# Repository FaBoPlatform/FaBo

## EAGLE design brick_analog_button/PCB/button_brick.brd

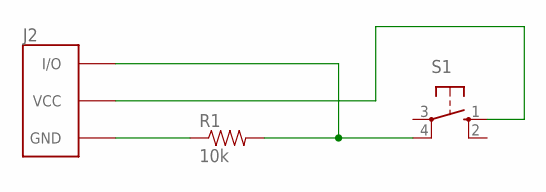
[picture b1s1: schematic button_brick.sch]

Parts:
J2: BRICK_3PIN
R1: 10k; AXIAL-0.4
S1: Button; B3F-10XX

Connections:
GND: J2.GND, R1.P$1 (1)
unnamed: J2.VCC, S1.1 (S)
unnamed: J2.IN/OUT (I/O), R1.P$2 (2), S1.4 (P1)

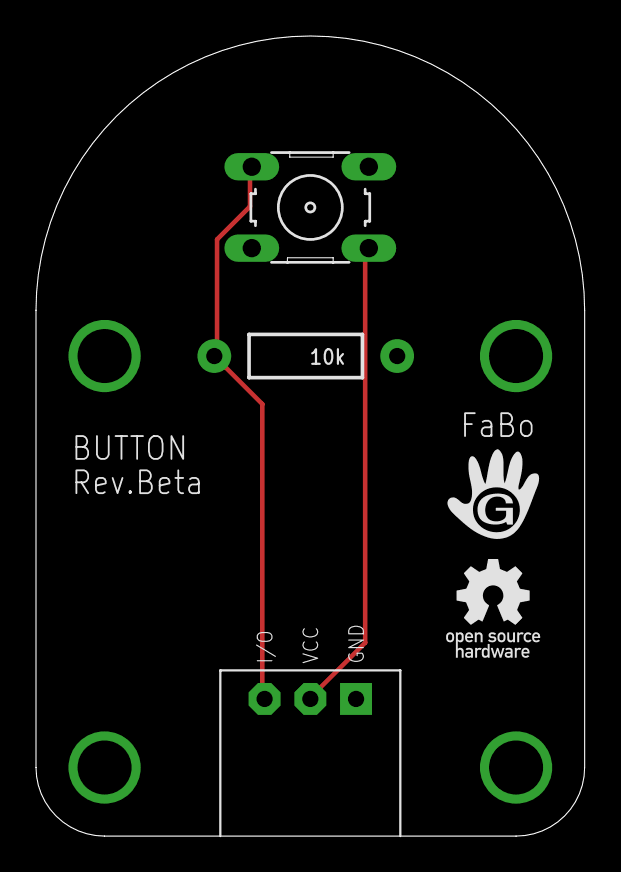
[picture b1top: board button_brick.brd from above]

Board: 2 copper layers, 30.5 x 44.5 mm, 5 parts (0 on the bottom side), 3 nets.

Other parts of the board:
U$2: LOGO_OSHW_T_M
U$3: LOGO_GCLUE_M

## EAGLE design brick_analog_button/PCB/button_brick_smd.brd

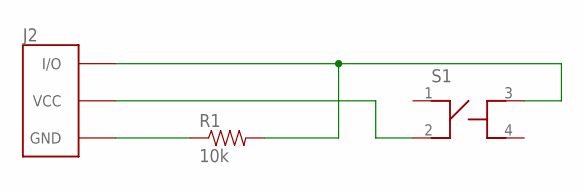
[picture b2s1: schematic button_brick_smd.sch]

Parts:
J2: BRICK_3PIN
R1: 10k; 0603-RES
S1: SWITCH-LS6J2M-T

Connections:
GND: J2.GND, R1.1
unnamed: J2.VCC, S1.2
unnamed: J2.IN/OUT (I/O), R1.2, S1.3

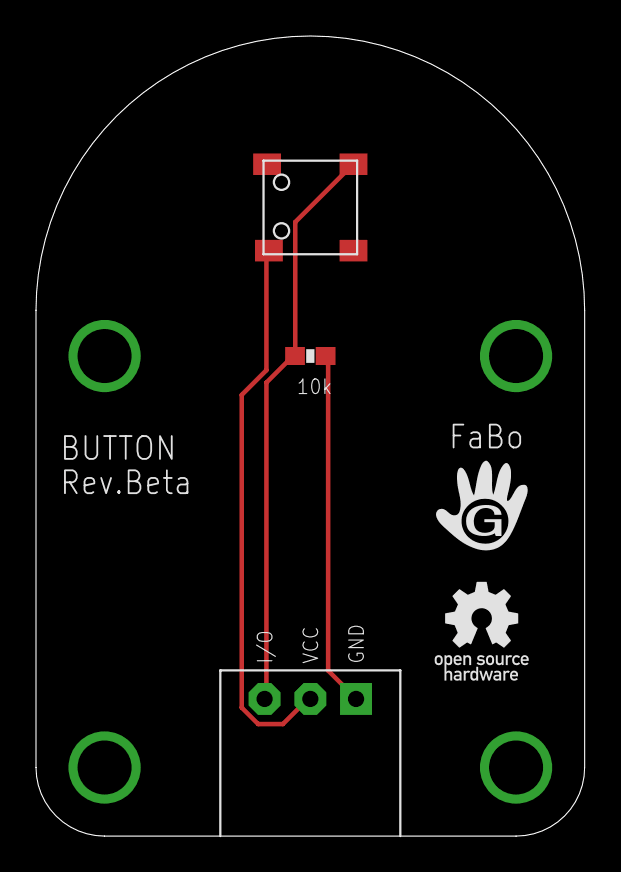
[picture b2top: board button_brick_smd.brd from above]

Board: 2 copper layers, 30.5 x 44.5 mm, 5 parts (0 on the bottom side), 3 nets.

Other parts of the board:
U$1: LOGO_GCLUE_M
U$2: LOGO_OSHW_T_M

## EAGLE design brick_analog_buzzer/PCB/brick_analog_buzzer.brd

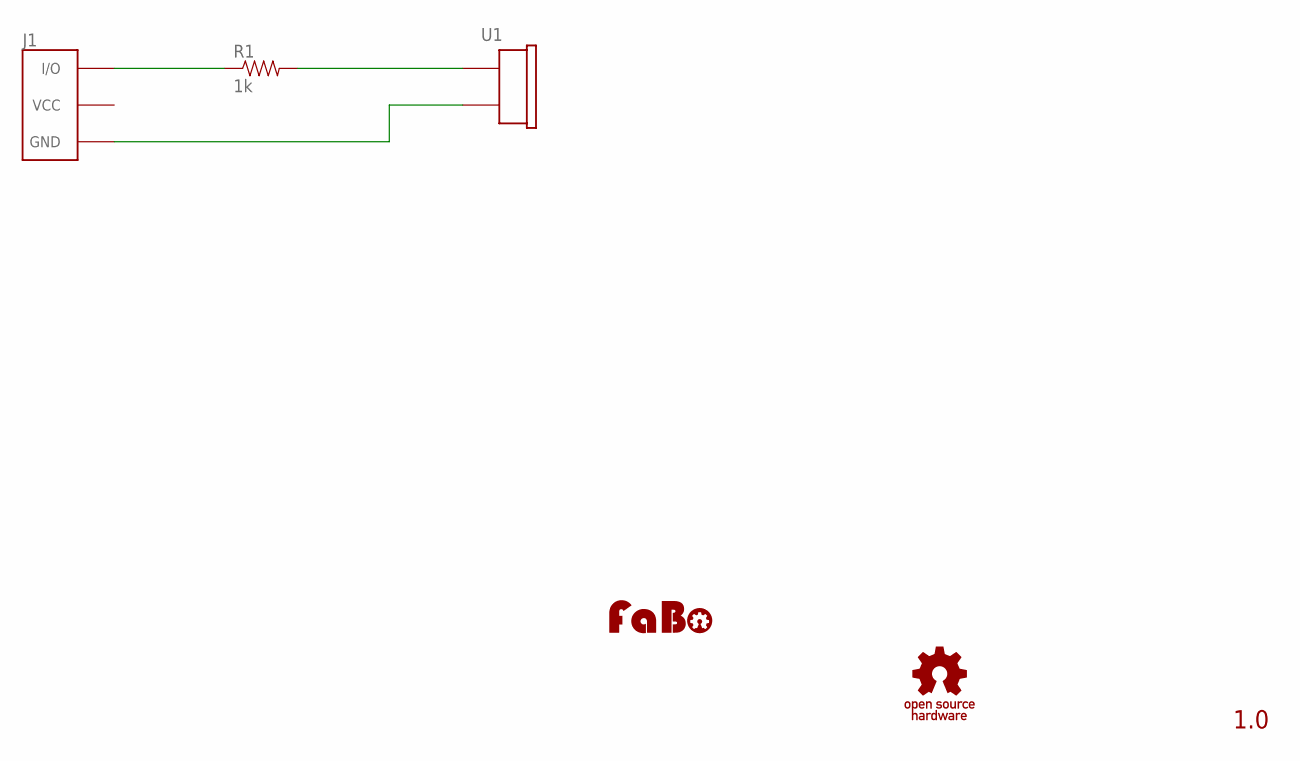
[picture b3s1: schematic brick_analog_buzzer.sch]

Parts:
J1: BRICK_3PIN_NORMAL; BRICK_3PIN
R1: 1k; RES-AXL-REGULAR
U1: BUZZER-PKM13EPYH4000; BUZZER-PKM13EPYH4000-A0
U$2: LOGO_OSHW_T-M; LOGO_OSHW_T_M
U$3: LOGO_FABO-M; LOGO_FABO_M

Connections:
GND: J1.GND, U1.2
unnamed: J1.IN/OUT (I/O), R1.P$1 (1)
unnamed: R1.P$2 (2), U1.1

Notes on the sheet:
1.0

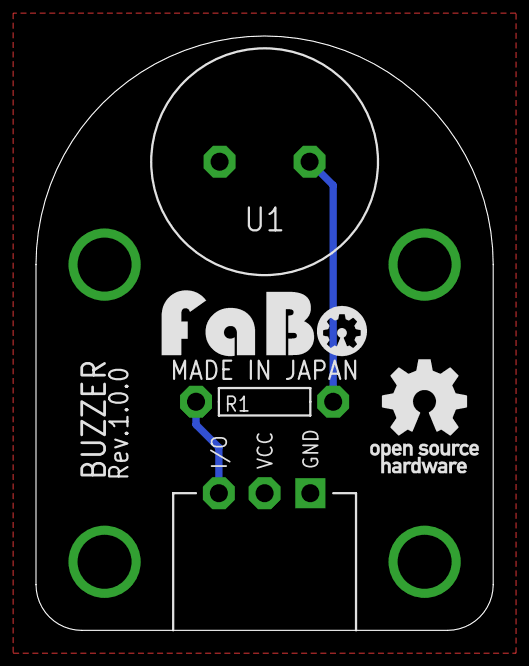
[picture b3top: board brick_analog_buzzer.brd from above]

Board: 2 copper layers, 25.4 x 33.0 mm, 5 parts (0 on the bottom side), 3 nets.

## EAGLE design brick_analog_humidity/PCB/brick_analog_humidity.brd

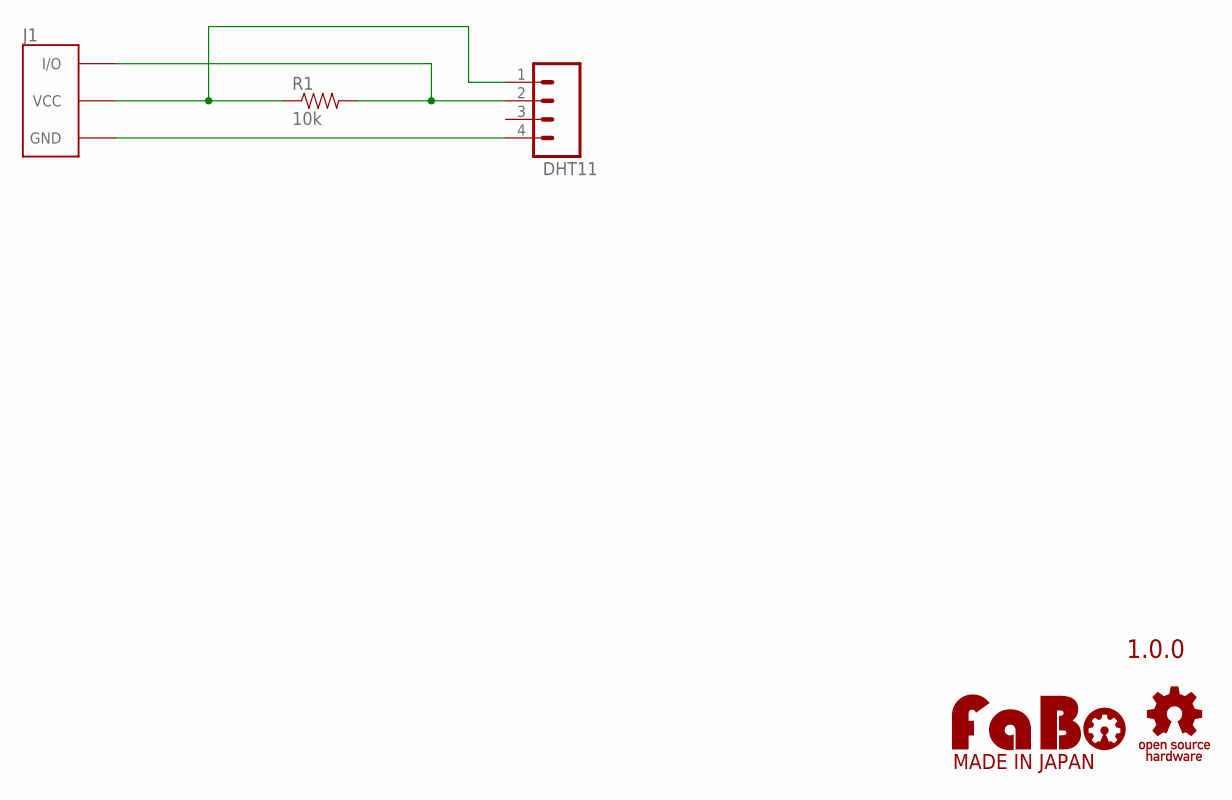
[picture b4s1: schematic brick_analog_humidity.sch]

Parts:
J1: BRICK_3PIN_NORMAL; BRICK_3PIN
JP1: DHT11; 1X04_LONGPADS
R1: 10k; RES-AXL-REGULAR
U$2: LOGO_OSHW-T_M; LOGO_OSHW_T_M
U$3: LOGO_FABO-M; LOGO_FABO_M

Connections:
GND: J1.GND, JP1.4
unnamed: J1.IN/OUT (I/O), JP1.2, R1.P$2 (2)
unnamed: J1.VCC, JP1.1, R1.P$1 (1)

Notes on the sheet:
1.0.0

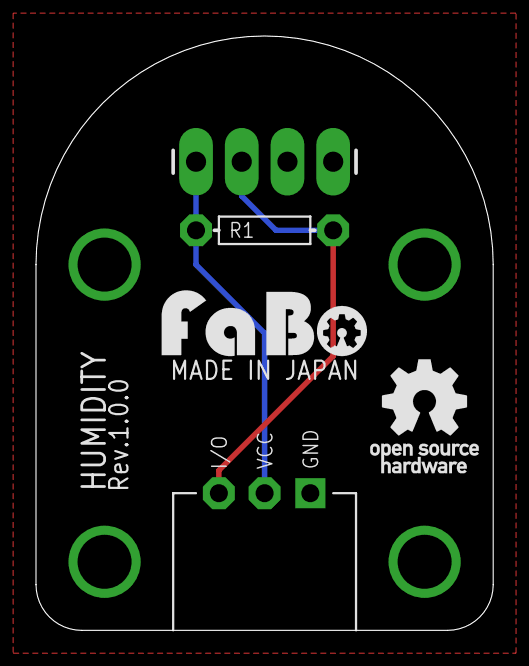
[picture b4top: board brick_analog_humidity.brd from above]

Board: 2 copper layers, 25.4 x 33.0 mm, 5 parts (0 on the bottom side), 3 nets.

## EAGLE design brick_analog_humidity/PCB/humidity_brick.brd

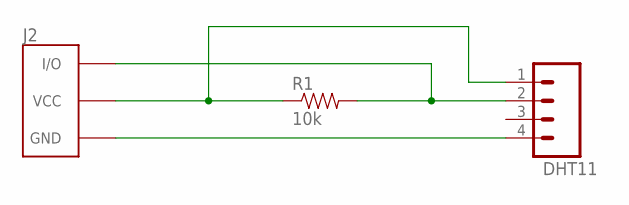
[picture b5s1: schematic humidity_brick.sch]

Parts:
J2: BRICK_3PIN
JP1: DHT11; 1X04_LONGPADS
R1: 10k; AXIAL-0.4

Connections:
GND: J2.GND, JP1.4
unnamed: J2.IN/OUT (I/O), JP1.2, R1.P$2 (2)
unnamed: J2.VCC, JP1.1, R1.P$1 (1)

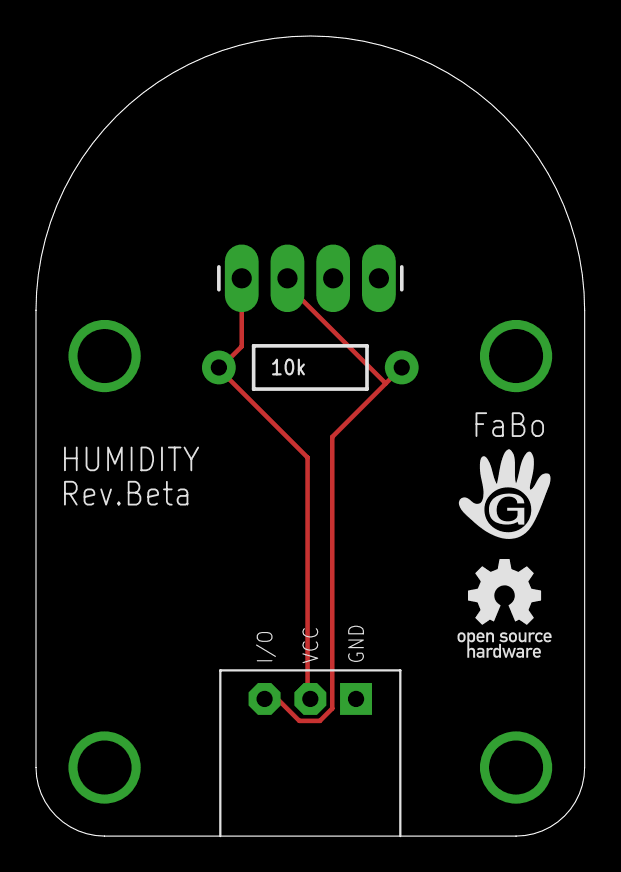
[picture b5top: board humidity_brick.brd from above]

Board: 2 copper layers, 30.5 x 44.5 mm, 5 parts (0 on the bottom side), 3 nets.

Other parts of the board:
U$1: LOGO_OSHW_T_M
U$3: LOGO_GCLUE_M

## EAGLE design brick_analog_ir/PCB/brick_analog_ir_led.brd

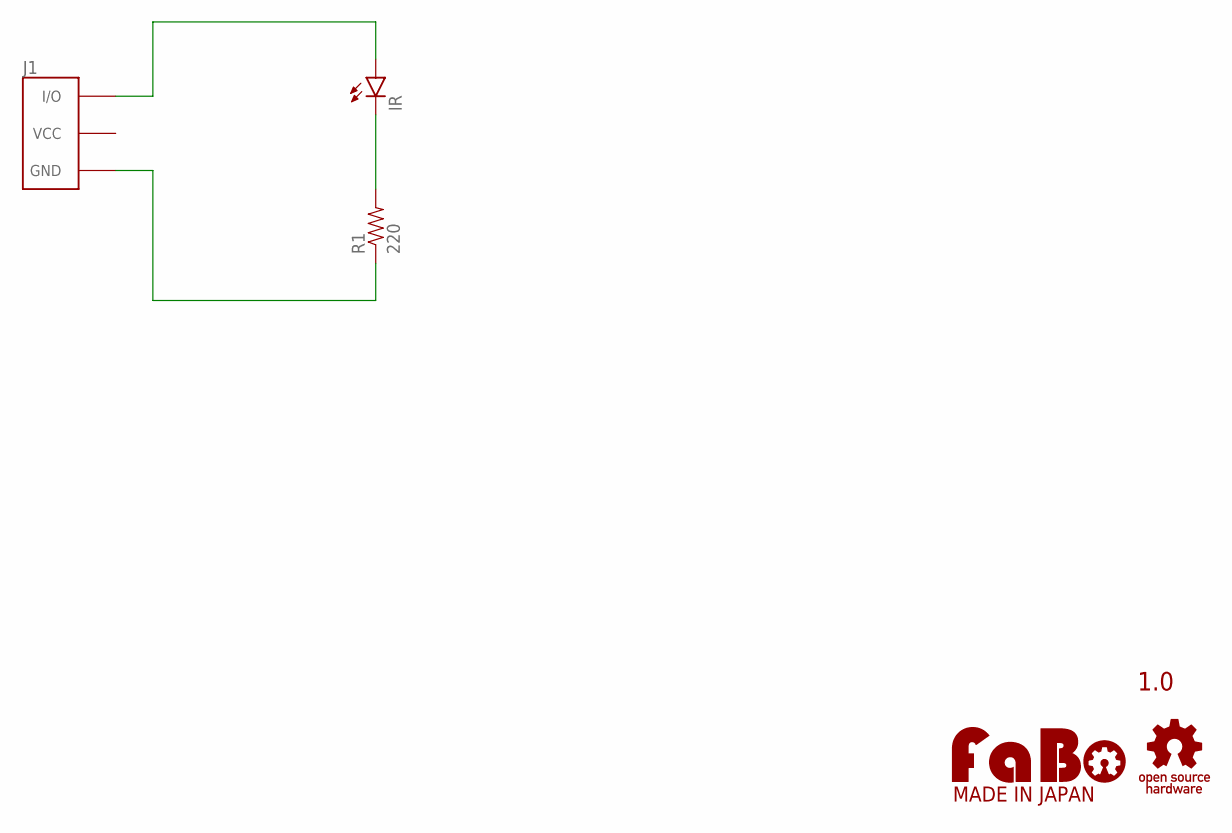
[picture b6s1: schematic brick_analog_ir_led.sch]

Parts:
IR: LED-5MM
J1: FABO_BRICK_3PIN
R1: 220; RES-AXL-REGULAR
U$2: LOGO_FABO-M; LOGO_FABO_M
U$3: LOGO_OSHW-T_M; LOGO_OSHW_T_M

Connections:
GND: J1.GND, R1.P$1 (1)
unnamed: IR.A, J1.IN/OUT (I/O)
unnamed: IR.K (C), R1.P$2 (2)

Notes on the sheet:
1.0

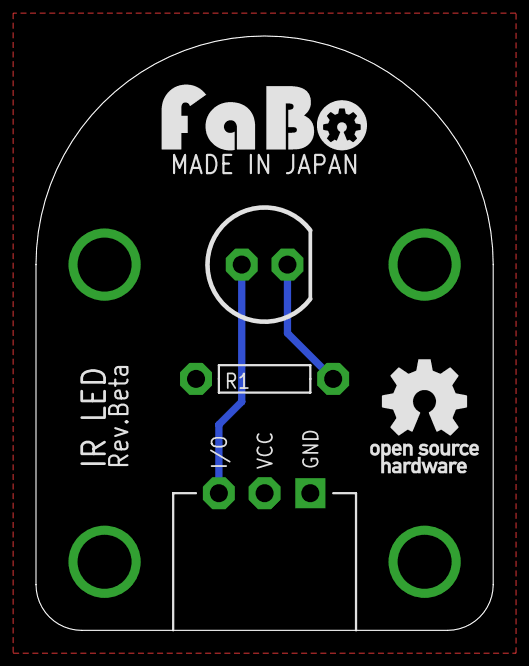
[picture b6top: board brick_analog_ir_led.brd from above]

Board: 2 copper layers, 25.4 x 33.0 mm, 5 parts (0 on the bottom side), 3 nets.

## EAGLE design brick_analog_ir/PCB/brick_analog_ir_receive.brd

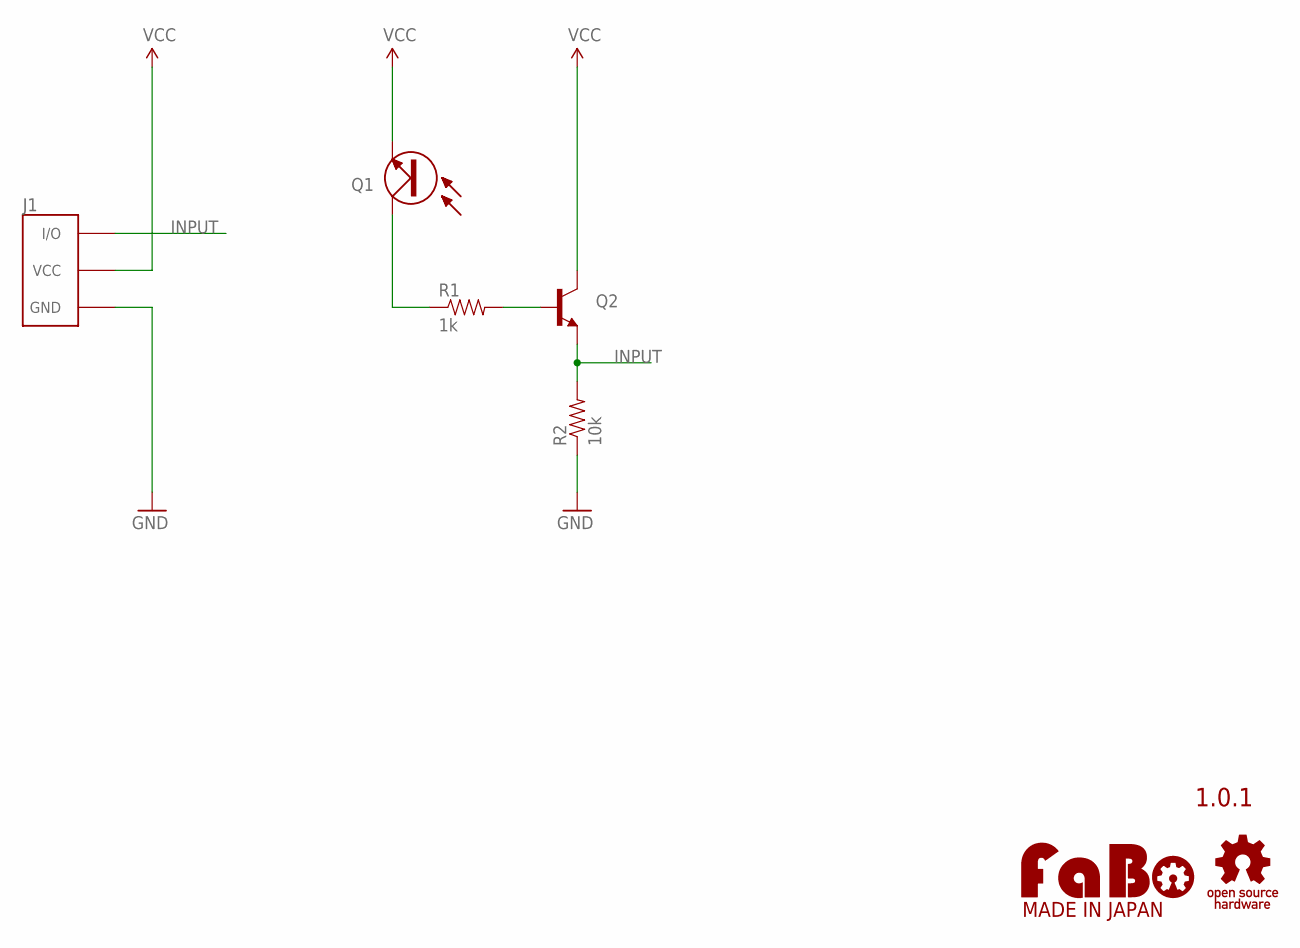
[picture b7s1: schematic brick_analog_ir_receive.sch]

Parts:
J1: FABO_BRICK_3PIN
Q1: L-51ROPT1D1; LED-5MM
Q2: NPN-2SC1815; TO-92
R1: 1k; RES-AXL-REGULAR
R2: 10k; RES-AXL-REGULAR
U$5: LOGO_FABO-M; LOGO_FABO_M
U$6: LOGO_OSHW-T_M; LOGO_OSHW_T_M

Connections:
GND: J1.GND, R2.P$1 (1)
INPUT: J1.IN/OUT (I/O), Q2.E, R2.P$2 (2)
unnamed: Q1.K (C), R1.P$1 (1)
unnamed: Q2.B, R1.P$2 (2)
VCC: J1.VCC, Q1.A (E), Q2.C

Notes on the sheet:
1.0.1

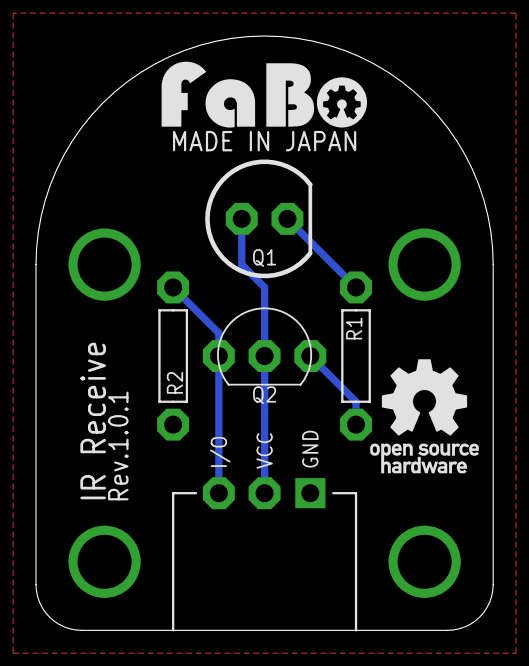
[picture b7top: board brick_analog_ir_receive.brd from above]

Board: 2 copper layers, 25.4 x 33.0 mm, 7 parts (0 on the bottom side), 5 nets.

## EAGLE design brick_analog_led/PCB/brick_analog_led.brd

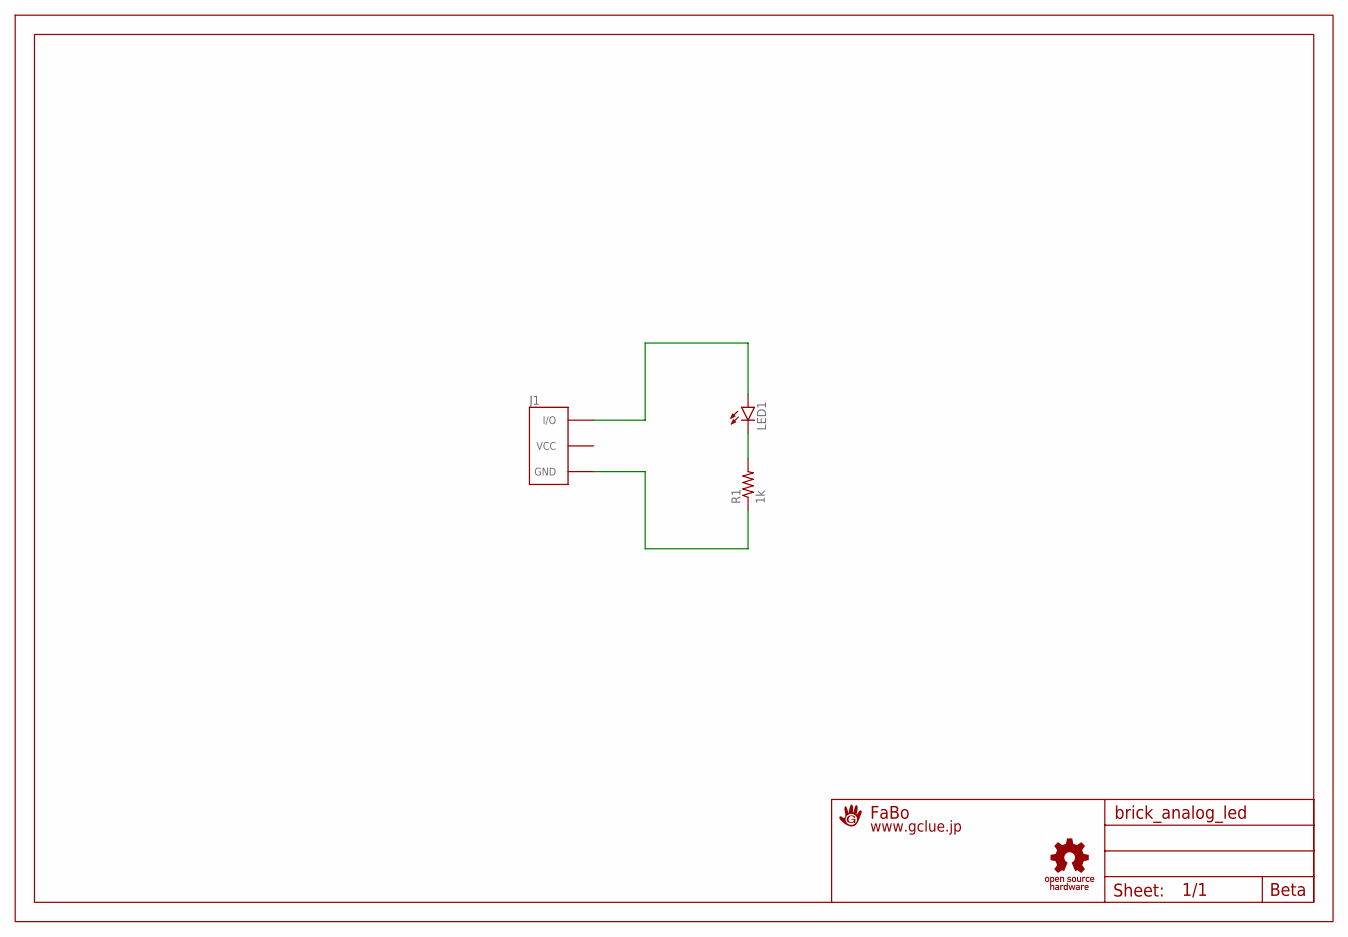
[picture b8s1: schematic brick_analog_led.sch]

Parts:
J1: BRICK_3PIN
LED1: LED-5MM
R1: 1k; RES-AXL-REGULAR
U$2: A4L-LOC-FABO_M; LOGO_FABO_M
U$4: LOGO_OSHW_T-M; LOGO_OSHW_T_M

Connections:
GND: J1.GND, R1.P$1 (1)
unnamed: J1.IN/OUT (I/O), LED1.A
unnamed: LED1.K (C), R1.P$2 (2)

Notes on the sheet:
Beta

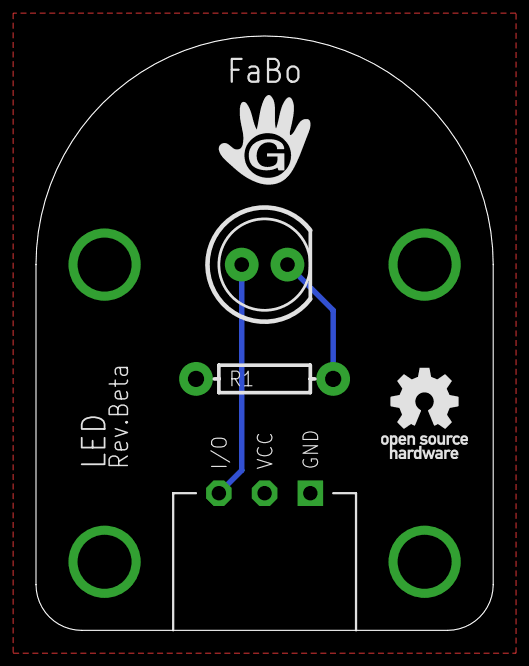
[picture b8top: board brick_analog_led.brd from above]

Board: 2 copper layers, 25.4 x 33.0 mm, 5 parts (0 on the bottom side), 3 nets.

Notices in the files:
parts and their libraries:
SparkFun-Resistors: Licensing: Creative Commons ShareAlike 4.0 International - https://creativecommons.org/licenses/by-sa/4.0
FaBo-etc: Released under the Creative Commons Attribution-ShareAlike 4.0 License
https://creativecommons.org/licenses/by-sa/4.0
FaBo-etc: Released under the Creative Commons
